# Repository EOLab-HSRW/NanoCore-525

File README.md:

# NanoCore 525

A simple DC-DC converter 5V 25W.

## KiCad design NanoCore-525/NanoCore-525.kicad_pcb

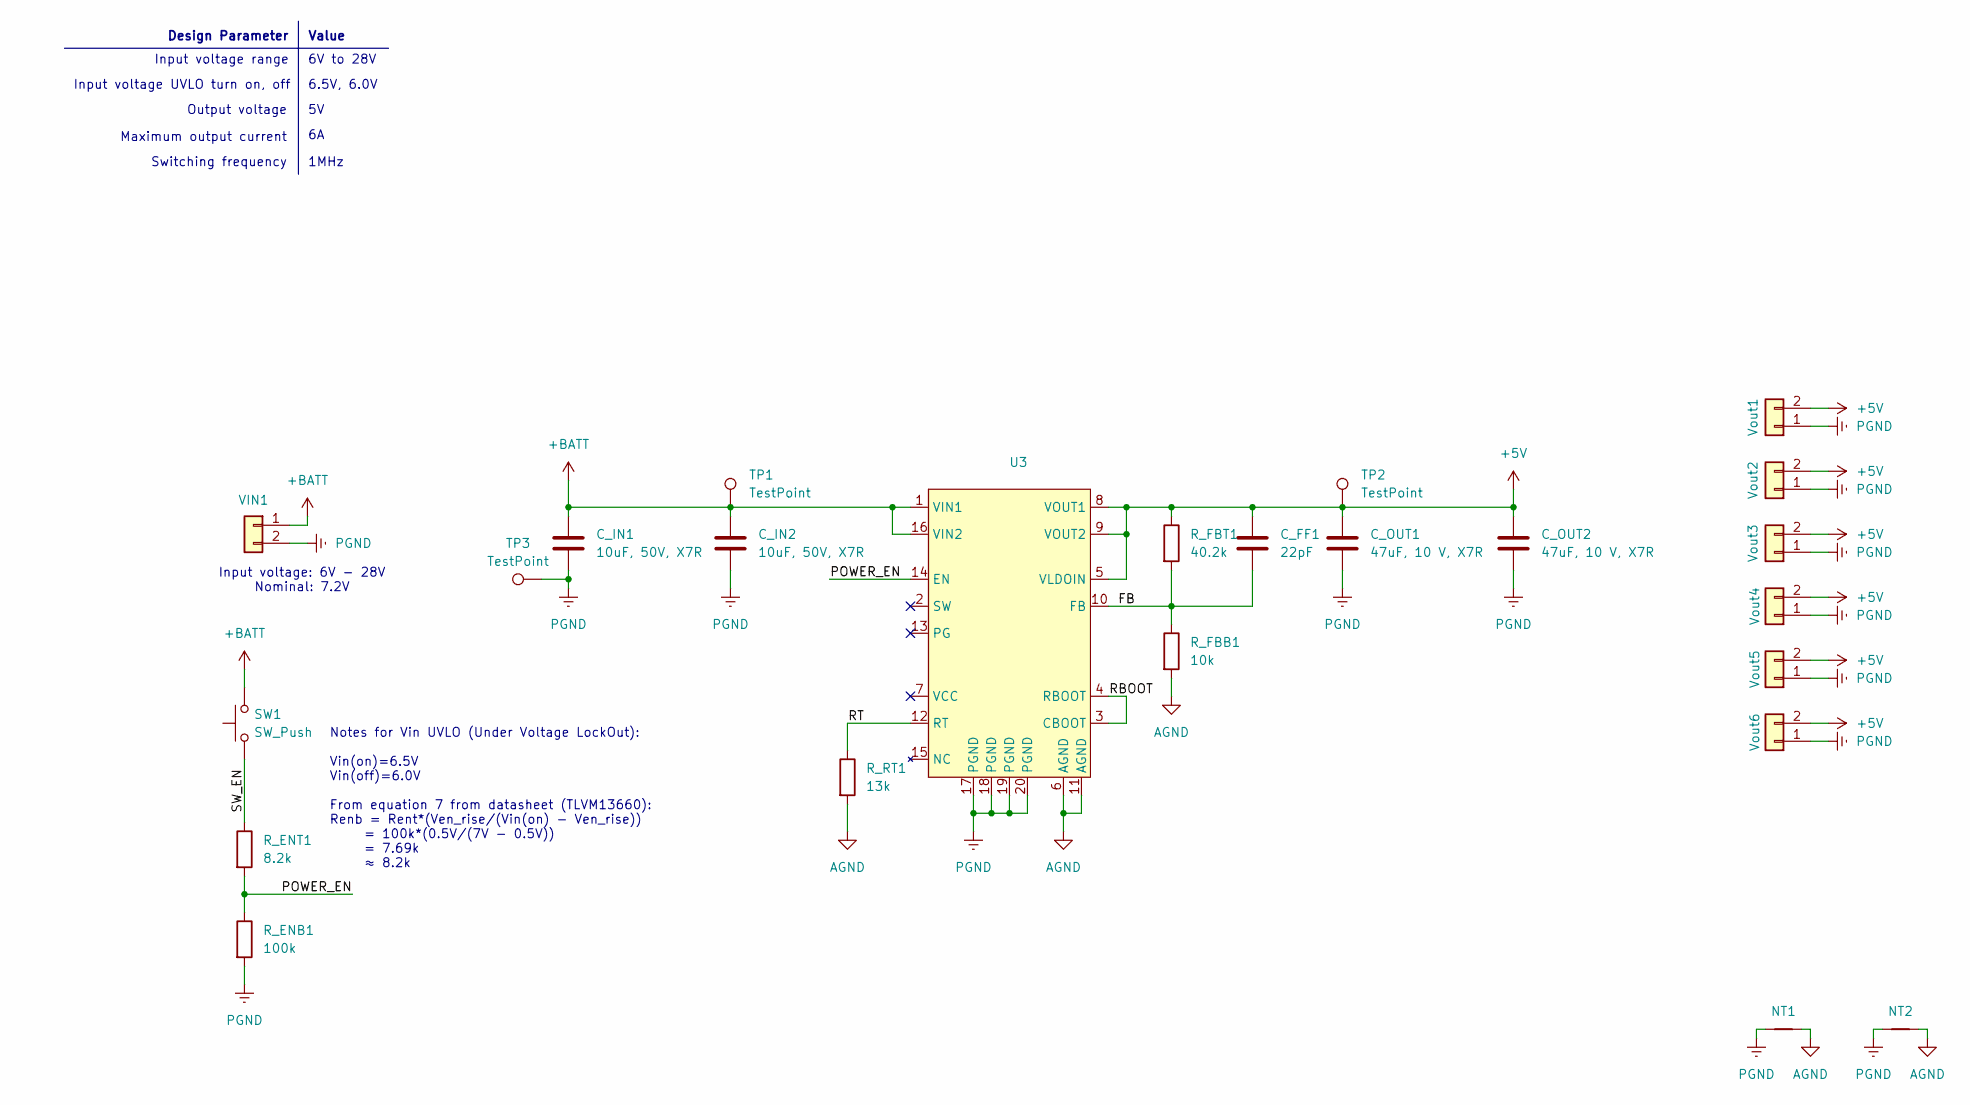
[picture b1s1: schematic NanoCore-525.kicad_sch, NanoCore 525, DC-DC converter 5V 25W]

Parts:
C_FF1: 22pF
C_IN1, C_IN2: 10uF, 50V, X7R; C_1210_3225Metric_Pad1.33x2.70mm_HandSolder; Mouser No 963-UMK325AB7106MM-T
C_OUT1, C_OUT2: 47uF, 10 V, X7R; C_1210_3225Metric_Pad1.33x2.70mm_HandSolder; Mouser No 187-CL32B476KPJNNNE
NT1, NT2: NetTie_2; NetTie-2_SMD_Pad2.0mm
R_ENB1: 100k; R_0402_1005Metric_Pad0.72x0.64mm_HandSolder
R_ENT1: 8.2k; R_0402_1005Metric_Pad0.72x0.64mm_HandSolder
R_FBB1: 10k; R_0402_1005Metric_Pad0.72x0.64mm_HandSolder
R_FBT1: 40.2k; R_0402_1005Metric_Pad0.72x0.64mm_HandSolder
R_RT1: 13k; R_0402_1005Metric_Pad0.72x0.64mm_HandSolder
SW1: SW_Push
TP1, TP2, TP3: TestPoint; TestPoint_Pad_D1.0mm
U3: B3QFN20_RDL_TEX; Mouser No 595-TLVM13660RDLR
VIN1: -; JST_VH_B2P-VH-B_1x02_P3.96mm_Vertical; Mouser No 306-306-B2PVHBLFSN
Vout1, Vout2, Vout3, Vout4, Vout5, Vout6: -; JST_VH_B2PS-VH_1x02_P3.96mm_Horizontal; Mouser No 306-B2PS-VHLFSN

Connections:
+5V: C_FF1.1, C_OUT1.1, C_OUT2.1, R_FBT1.1, TP2.1, U3.5 (VLDOIN), U3.8 (VOUT1), U3.9 (VOUT2), Vout1.2, Vout2.2, Vout3.2, Vout4.2, Vout5.2, Vout6.2
+BATT: C_IN1.1, C_IN2.1, SW1.2, TP1.1, U3.1 (VIN1), U3.16 (VIN2), VIN1.1
/FB: C_FF1.2, R_FBB1.1, R_FBT1.2, U3.10 (FB)
/POWER_EN: R_ENB1.1, R_ENT1.2, U3.14 (EN)
/RBOOT: U3.3 (CBOOT), U3.4 (RBOOT)
/RT: R_RT1.1, U3.12 (RT)
/SW_EN: R_ENT1.1, SW1.1
AGND: NT1.2, NT2.2, R_FBB1.2, R_RT1.2, U3.6 (AGND), U3.11 (AGND)
PGND: C_IN1.2, C_IN2.2, C_OUT1.2, C_OUT2.2, NT1.1, NT2.1, R_ENB1.2, TP3.1, U3.17 (PGND), U3.18 (PGND), U3.19 (PGND), U3.20 (PGND), VIN1.2, Vout1.1, Vout2.1, Vout3.1, Vout4.1, Vout5.1, Vout6.1

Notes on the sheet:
Design Parameter
Input voltage: 6V - 28V Nominal: 7.2V
Value
Maximum output current
6.5V, 6.0V
Input voltage UVLO turn on, off
Switching frequency
Notes for Vin UVLO (Under Voltage LockOut): Vin(on)=6.5V Vin(off)=6.0V From equation 7 from datasheet (TLVM13660): Renb = Rent*(Ven_rise/(Vin(on) - Ven_rise)) = 100k*(0.5V/(7V - 0.5V)) = 7.69k ≈ 8.2k
1MHz
Input voltage range
6V to 28V
Output voltage

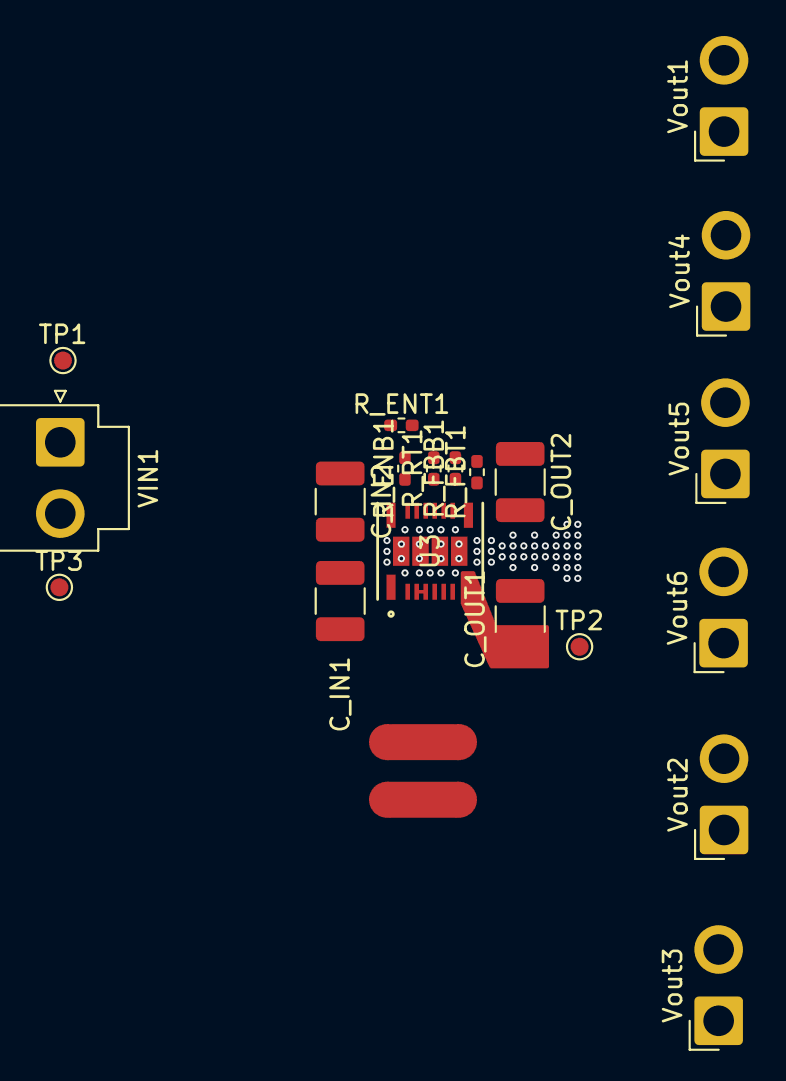
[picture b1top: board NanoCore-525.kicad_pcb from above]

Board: 2 copper layers, 22 parts (0 on the bottom side), 8 nets.

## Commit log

2024-11-19 init
